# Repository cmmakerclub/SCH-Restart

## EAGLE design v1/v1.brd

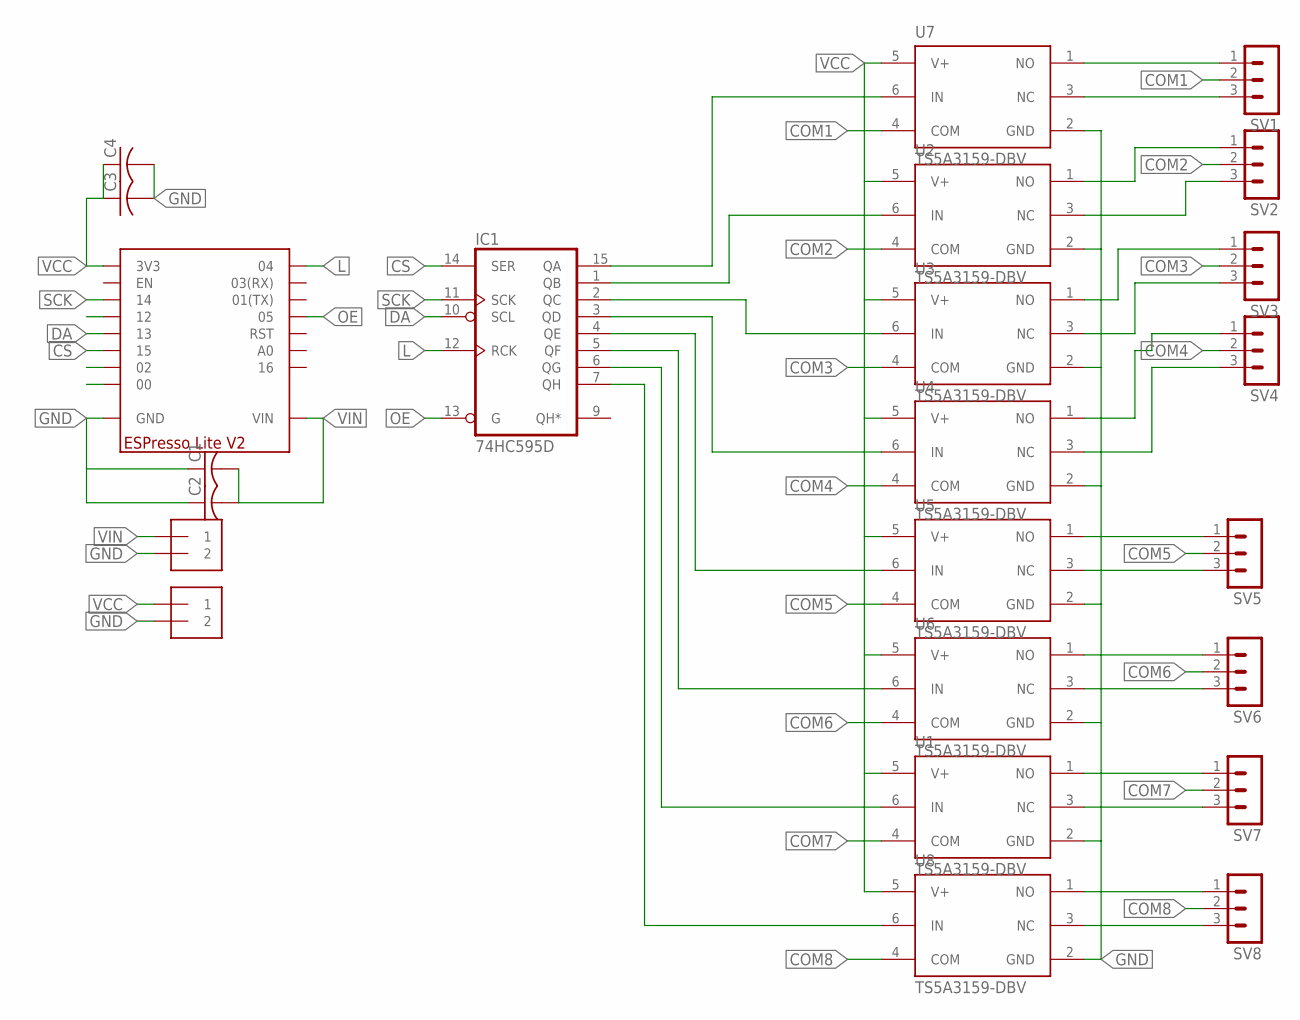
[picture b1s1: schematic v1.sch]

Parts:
C1, C2, C3, C4: C-USC0805; C0805
IC1: 74HC595D; SO16
J1, J2: 1X2-3.5MM
SV1, SV2, SV3, SV4, SV5, SV6, SV7, SV8: MA03-1
U1, U2, U3, U4, U5, U6, U7, U8: TS5A3159-DBV; SOT23-6L
U$1: ESPRESSO-LITE-V2

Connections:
COM1: SV1.2, U7.4 (COM)
COM2: SV2.2, U2.4 (COM)
COM3: SV3.2, U3.4 (COM)
COM4: SV4.2, U4.4 (COM)
COM5: SV5.2, U5.4 (COM)
COM6: SV6.2, U6.4 (COM)
COM7: SV7.2, U1.4 (COM)
COM8: SV8.2, U8.4 (COM)
CS: IC1.14 (SER), U$1.15
DA: IC1.10 (SCL), U$1.13
GND: C1.1, C2.1, C3.2, C4.2, IC1.8 (GND), J1.2, J2.2, U1.2 (GND), U2.2 (GND), U3.2 (GND), U4.2 (GND), U5.2 (GND), U6.2 (GND), U7.2 (GND), U8.2 (GND), U$1.GND1 (GND), U$1.GND2 (GND), U$1.GND3 (GND)
L: IC1.12 (RCK), U$1.04
unnamed: SV3.3, U3.3 (NC)
unnamed: SV1.1, U7.1 (NO)
unnamed: SV1.3, U7.3 (NC)
unnamed: SV2.1, U2.1 (NO)
unnamed: SV2.3, U2.3 (NC)
unnamed: SV3.1, U3.1 (NO)
unnamed: SV4.1, U4.1 (NO)
unnamed: SV4.3, U4.3 (NC)
unnamed: SV5.1, U5.1 (NO)
unnamed: SV5.3, U5.3 (NC)
unnamed: SV6.1, U6.1 (NO)
unnamed: SV6.3, U6.3 (NC)
unnamed: SV7.1, U1.1 (NO)
unnamed: SV7.3, U1.3 (NC)
unnamed: SV8.1, U8.1 (NO)
unnamed: SV8.3, U8.3 (NC)
unnamed: IC1.7 (QH), U8.6 (IN)
unnamed: IC1.6 (QG), U1.6 (IN)
unnamed: IC1.5 (QF), U6.6 (IN)
unnamed: IC1.4 (QE), U5.6 (IN)
unnamed: IC1.3 (QD), U4.6 (IN)
unnamed: IC1.2 (QC), U3.6 (IN)
unnamed: IC1.1 (QB), U2.6 (IN)
unnamed: IC1.15 (QA), U7.6 (IN)
OE: IC1.13 (G), U$1.05
SCK: IC1.11 (SCK), U$1.14
VCC: C3.1, C4.1, IC1.16 (VCC), J2.1, U1.5 (V+), U2.5 (V+), U3.5 (V+), U4.5 (V+), U5.5 (V+), U6.5 (V+), U7.5 (V+), U8.5 (V+), U$1.3V3
VIN: C1.2, C2.2, J1.1, U$1.VIN1 (VIN), U$1.VIN2 (VIN)

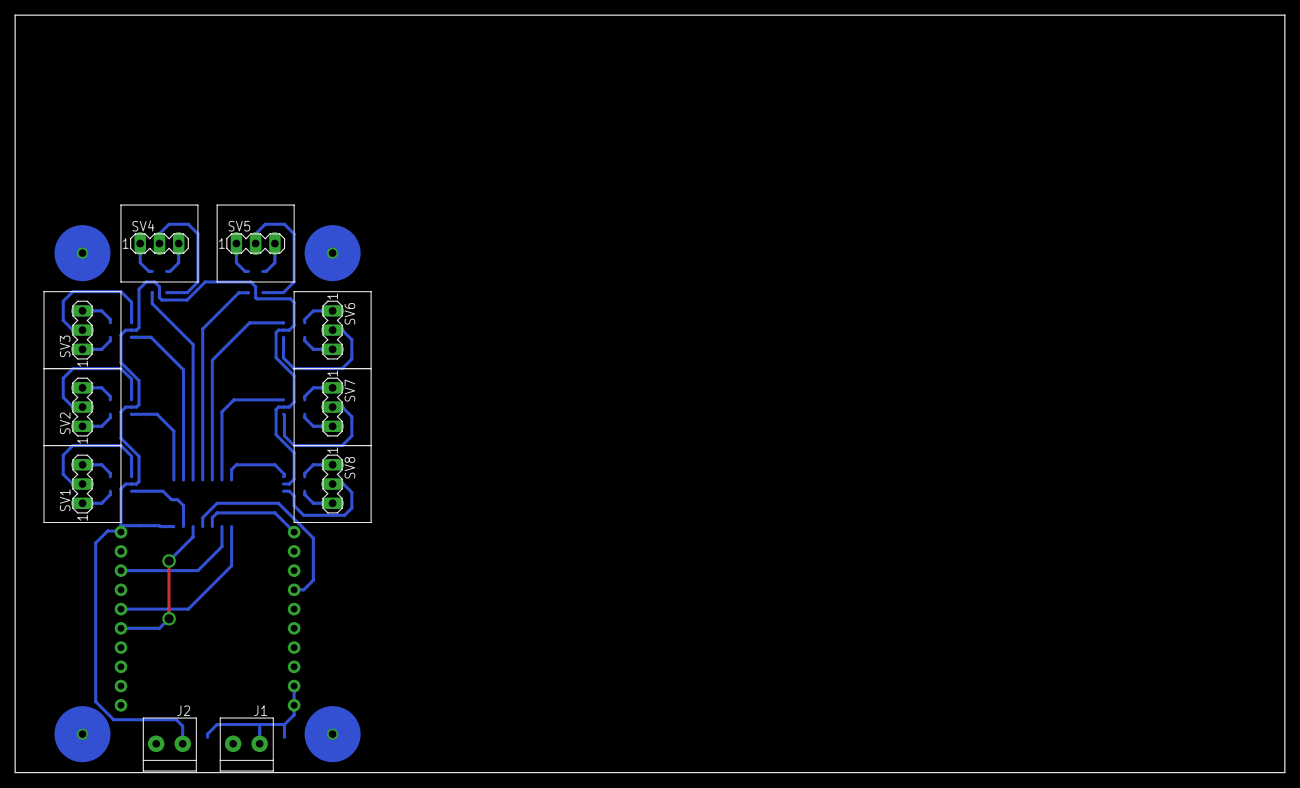
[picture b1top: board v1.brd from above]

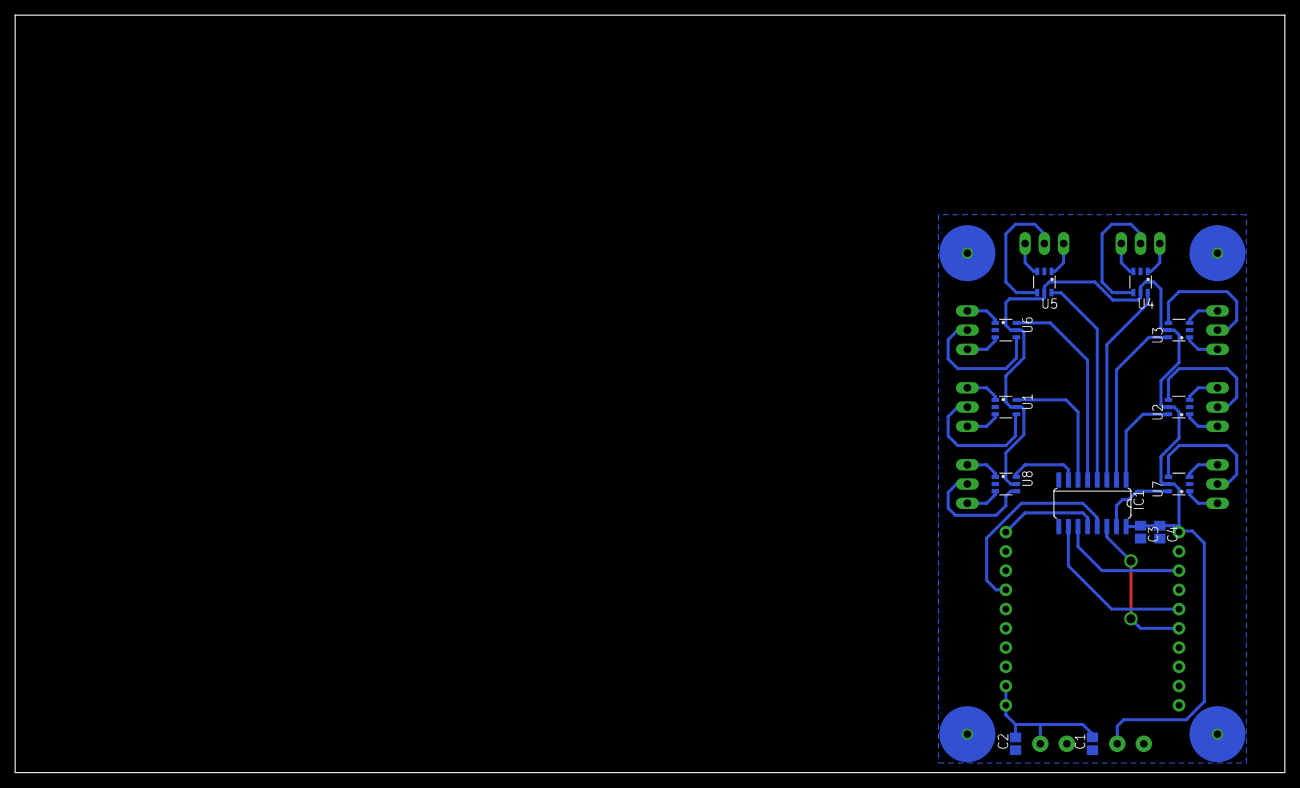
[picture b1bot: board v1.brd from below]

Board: 2 copper layers, 167.6 x 100.0 mm, 24 parts (13 on the bottom side), 40 nets.

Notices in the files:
parts and their libraries:
m-pad-2.1: License : GNU General Public License version 2 (see bottom)
